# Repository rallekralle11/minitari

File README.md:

Not easy to put together, but functional at least. I'll improve it later.

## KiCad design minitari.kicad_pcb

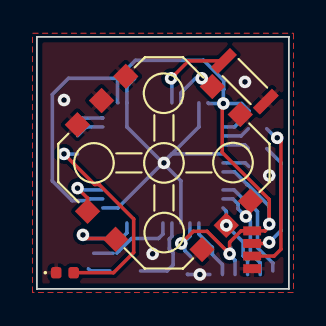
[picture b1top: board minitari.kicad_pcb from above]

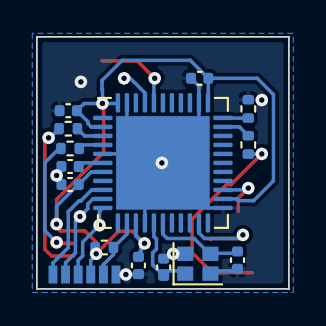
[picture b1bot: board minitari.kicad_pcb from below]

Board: 2 copper layers, 14.0 x 14.0 mm, 19 parts (15 on the bottom side), 20 nets.

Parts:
C1, C2: crystal_TBD; C_0402_1005Metric
C3: 1µF; C_0402_1005Metric
C4, C6, C7, C8: 100nF; C_0402_1005Metric
D1: LED; LED_0402_1005Metric
J2: Conn_01x06; PinSocket_1x06_P1.27mm_Vertical
J3: Conn_01x04; PinSocket_1x04_P1.27mm_Vertical
R1, R2: 22Ω; R_0402_1005Metric
R3, R4: 10kΩ; R_0402_1005Metric
R5: 1kΩ; R_0402_1005Metric
SW1: JS_1300_keypad
SW3: SW_MEC_5G; TL3780
U1: ATmega32U4-M; QFN-44-1EP_7x7mm_P0.5mm_EP5.2x5.2mm
Y1: 16mhz; Crystal_SMD_2016-4Pin_2.0x1.6mm

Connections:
/D13: R5.1, U1.32 (PC7)
D1/TX: SW1.4 (2_1), U1.21 (PD3)
D4: SW1.5 (5_1), U1.25 (PD4)
D14/MISO: J2.2, SW1.2 (3_1), U1.11 (PB3)
D15/SCK: J2.1, U1.9 (PB1)
D16/MOSI: J2.3, SW1.1 (1_1), U1.10 (PB2)
D22: SW3.3 (B), U1.40 (PF1)
D23: SW1.9 (4_1), U1.41 (PF0)
GND: C1.1, C2.1, C3.1, C4.2, C6.2, C7.1, C8.1, D1.1 (K), J2.6, J3.1, R4.2, SW1.3 (2_2), SW1.6 (5_2), SW1.7 (3_2), SW1.8 (4_2), SW1.10 (1_2), SW3.1 (A), U1.5 (UGND), U1.15 (GND), U1.23 (GND), U1.35 (GND), U1.43 (GND), U1.45 (GND), Y1.2, Y1.4
unnamed: D1.2 (A), R5.2
unnamed: J3.2, R2.2
unnamed: J3.3, R1.1
unnamed: R1.2, U1.4 (D+)
unnamed: R2.1, U1.3 (D-)
unnamed: C3.2, U1.6 (UCAP)
unnamed: C1.2, U1.17 (XTAL1), Y1.3
unnamed: C2.2, U1.16 (XTAL2), Y1.1
unnamed: R4.1, U1.33 (~HWB/PE2)
RST: J2.4, R3.2, U1.13 (~RESET)
VCC: C4.1, C6.1, C7.2, C8.2, J2.5, J3.4, R3.1, U1.2 (UVCC), U1.7 (VBUS), U1.14 (VCC), U1.24 (AVCC), U1.34 (VCC), U1.44 (AVCC)

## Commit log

2024-09-22 init
